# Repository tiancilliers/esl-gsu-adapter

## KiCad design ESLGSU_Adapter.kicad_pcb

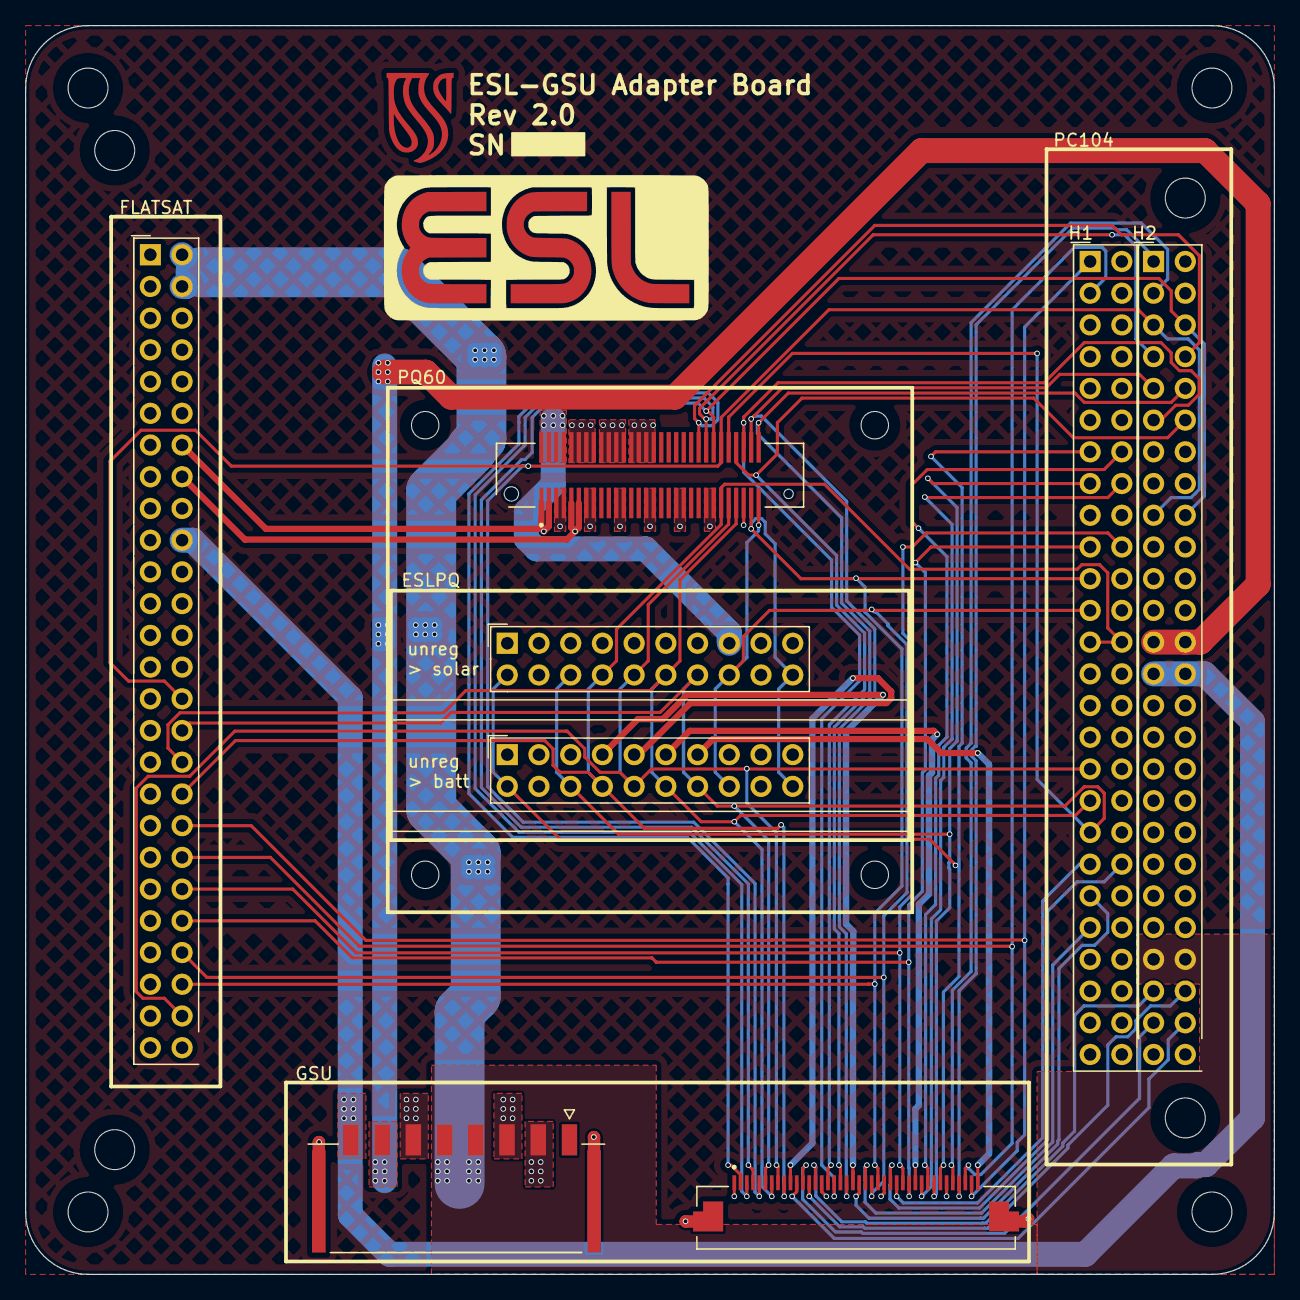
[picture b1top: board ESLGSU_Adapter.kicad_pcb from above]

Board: 4 copper layers, 100.0 x 100.0 mm, 20 parts (0 on the bottom side), 41 nets.

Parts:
H1, H2, H3, H4, H5, H7, H8, H9: MountingHole; MountingHole_3.2mm_M3_DIN965_Keepout
H6, H10, H11, H12: MountingHole; MountingHole_2.2mm_M2_DIN965_Keepout
J1: AMPHENOL_62684-401100ALF
J2: 1054301108; MOLEX_1054301108
J3, J5, J6: Conn_02x26_Odd_Even; PinSocket_2x26_P2.54mm_Vertical_OddEven
J4, J7: Conn_02x10_Odd_Even; PinHeader_2x10_P2.54mm_Vertical_PQ
J8: Conn_02x30_Odd_Even; HIROSE_FX8C-60P-SV6_91_

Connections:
/3V3_S1: J1.40, J3.14, J4.7, J5.52, J7.7, J8.1, J8.3
/3V3_S2: J1.30, J3.16, J4.6, J5.50, J7.6, J8.9, J8.11
/5V_S1: J1.20, J3.8, J4.4, J5.51, J7.4
/5V_S2: J1.10, J3.10, J4.5, J5.49, J7.5
/BUS_3V3: J2.8, J3.20, J4.8, J6.27, J6.28, J7.8, J8.2, J8.4, J8.6, J8.8
/BUS_5V: J2.7, J3.6, J4.3, J6.25, J6.26, J7.3
/BUS_CH1: J2.2, J6.23, J6.24
/BUS_UNREG: J2.4, J2.5, J3.2, J3.4, J4.10, J6.45, J6.46, J7.1, J8.18, J8.20, J8.22, J8.24
/CAN1_H: J1.38, J3.40, J5.3
/CAN1_L: J1.39, J3.38, J5.1
/CAN2_H: J1.36, J6.3
/CAN2_L: J1.37, J6.1
/GPIO_1: J1.09 (Pin_9), J3.36, J4.17, J5.25, J5.26, J7.17, J8.49
/GPIO_2: J1.08 (Pin_8), J3.50, J4.16, J5.33, J7.16, J8.51
/GPIO_3: J1.07 (Pin_7), J3.34, J4.15, J5.35, J7.15, J8.53
/GPIO_4: J1.06 (Pin_6), J3.32, J4.14, J5.37, J7.14, J8.52
/GPIO_5: J1.05 (Pin_5), J3.30, J6.5, J6.17, J8.50
/GPIO_6: J1.04 (Pin_4), J6.6, J6.18, J8.48
/GPIO_7: J1.03 (Pin_3), J6.7, J6.19, J8.46
/GPIO_8: J1.02 (Pin_2), J6.8, J6.20, J8.44
/I2C1_SCL: J1.24, J3.48, J4.11, J5.21, J7.11, J8.57
/I2C1_SDA: J1.23, J3.46, J4.13, J5.23, J7.13, J8.59
/I2C2_SCL: J1.22, J5.43
/I2C2_SDA: J1.21, J5.41
/RS4851_A: J1.34, J4.20, J5.13, J7.20
/RS4851_B: J1.33, J4.18, J5.15, J7.18
/RS4852_A: J1.32, J5.14
/RS4852_B: J1.31, J5.16
/SPI1_MISO: J1.19, J6.9, J8.58
/SPI1_MOSI: J1.18, J6.10, J8.60
/SPI1_NSS: J1.16, J6.12, J8.54
/SPI1_SCK: J1.17, J6.11, J8.56
/SPI2_MISO: J1.14, J6.47
/SPI2_MOSI: J1.13, J6.48
/SPI2_NSS: J1.11, J6.50
/SPI2_SCK: J1.12, J6.49
/UART1_RX: J1.28, J3.42, J5.20
/UART1_TX: J1.29, J3.44, J5.19
/UART2_RX: J1.26, J5.40
/UART2_TX: J1.27, J5.39
GND: J1.01 (Pin_1), J1.15, J1.25, J1.35, J1.S1 (MountPin), J1.S2 (MountPin), J2.3, J2.6, J2.S1 (MountPin), J2.S2 (MountPin), J3.1, J3.3, J3.5, J3.7, J3.9, J3.13, J3.15, J3.19, J3.39, J3.45, J4.2, J4.9, J4.12, J4.19, J5.34, J6.29, J6.30, J6.31, J6.32, J7.2, J7.9, J7.12, J7.19, J8.5, J8.7, J8.10, J8.12, J8.13, J8.14, J8.15, J8.16, J8.21, J8.23, J8.26, J8.28, J8.29, J8.30, J8.31, J8.32, J8.37, J8.39, J8.45, J8.47, J8.55

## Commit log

2025-03-25 Updated PCB
